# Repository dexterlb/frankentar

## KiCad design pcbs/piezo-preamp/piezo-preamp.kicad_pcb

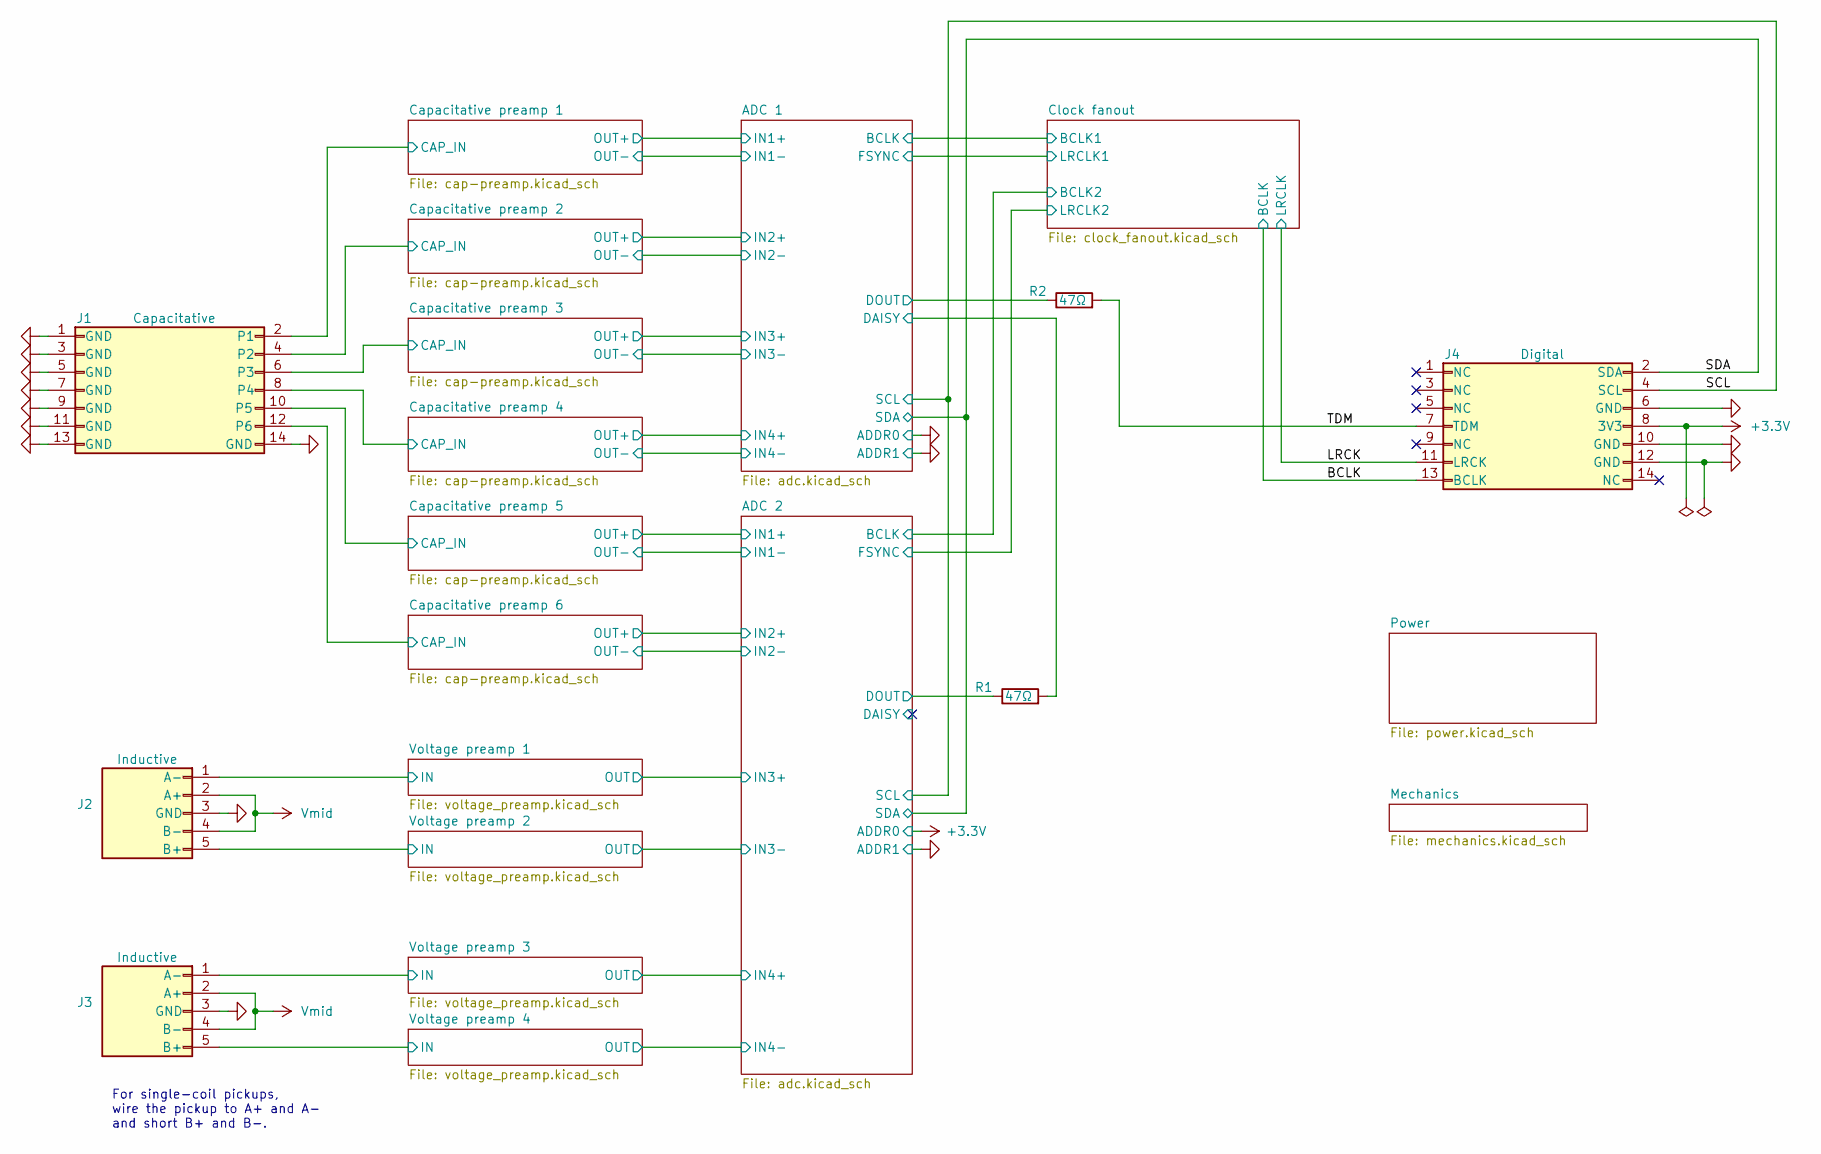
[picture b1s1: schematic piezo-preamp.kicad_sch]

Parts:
J1, J4: Conn_02x07_Odd_Even; PinHeader_2x07_P2.54mm_Vertical; MPN Header_02x07
J2, J3: Header_01x05; PinHeader_1x05_P2.54mm_Vertical
R1, R2: 47Ω; R_0805_2012Metric; MPN R 47Ω 125mW 1% 0805

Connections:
+3.3V: J4.8; also elsewhere on the board
/ADC 1/DAISY: R1.2; also elsewhere on the board
/ADC 1/DOUT: R2.1; also elsewhere on the board
/ADC 2/DOUT: R1.1; also elsewhere on the board
/BCLK: J4.13 (Pin_9); also elsewhere on the board
/Capacitative preamp 1/CAP_IN: J1.2; also elsewhere on the board
/Capacitative preamp 2/CAP_IN: J1.4; also elsewhere on the board
/Capacitative preamp 3/CAP_IN: J1.6; also elsewhere on the board
/Capacitative preamp 4/CAP_IN: J1.8; also elsewhere on the board
/Capacitative preamp 5/CAP_IN: J1.10; also elsewhere on the board
/Capacitative preamp 6/CAP_IN: J1.12; also elsewhere on the board
/LRCK: J4.11 (Pin_9); also elsewhere on the board
/SCL: J4.4; also elsewhere on the board
/SDA: J4.2; also elsewhere on the board
/TDM: J4.7, R2.2
/Voltage preamp 1/IN: J2.1; also elsewhere on the board
/Voltage preamp 2/IN: J2.5; also elsewhere on the board
/Voltage preamp 3/IN: J3.1; also elsewhere on the board
/Voltage preamp 4/IN: J3.5; also elsewhere on the board
GND: J1.1, J1.3, J1.5, J1.7, J1.9, J1.11 (Pin_9), J1.13 (Pin_9), J1.14 (Pin_12), J2.3, J3.3, J4.6, J4.10, J4.12; also elsewhere on the board
Vmid: J2.2, J2.4, J3.2, J3.4; also elsewhere on the board

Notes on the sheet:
For single-coil pickups, wire the pickup to A+ and A- and short B+ and B-.

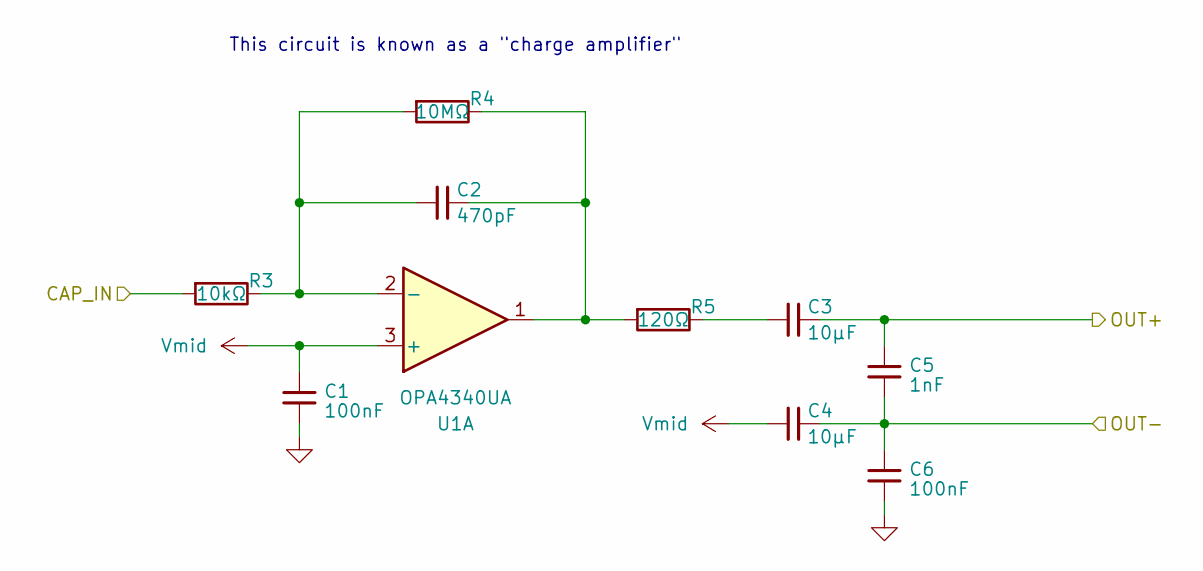
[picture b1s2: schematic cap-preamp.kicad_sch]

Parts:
C1, C6: 100nF; C_0805_2012Metric; MPN C 100nF 16V 0805
C2: 470pF; C_0805_2012Metric; MPN C 470pF 16V 0805; LCSC C1743
C3, C4: 10μF; C_0805_2012Metric; MPN C 10μF 50V 0805; LCSC C440198
C5: 1nF; C_0805_2012Metric; MPN C 1nF 16V 0805
R3: 10kΩ; R_0805_2012Metric; MPN R 10kΩ 125mW 1% 0805
R4: 10MΩ; R_0805_2012Metric; MPN R 10MΩ 125mW 1% 0805; LCSC C26108
R5: 120Ω; R_0805_2012Metric; MPN R 120Ω 125mW 1% 0805
U1: OPA4340UA; SOIC-14_3.9x8.7mm_P1.27mm; MPN OPA4340UA; LCSC C21713888

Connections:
/ADC 1/IN1+: C3.2, C5.1; also elsewhere on the board
/ADC 1/IN1-: C4.2, C5.2, C6.1; also elsewhere on the board
/Capacitative preamp 1/CAP_IN: R3.2; also elsewhere on the board
GND: C1.2, C6.2; also elsewhere on the board
unnamed: C2.2, R4.1, R5.2, U1.1
unnamed: C3.1, R5.1
unnamed 47: U1.7; also elsewhere on the board
unnamed 49: U1.8; also elsewhere on the board
unnamed 51: U1.14; also elsewhere on the board
unnamed: C2.1, R3.1, R4.2, U1.2 (-)
unnamed 64: U1.6 (-); also elsewhere on the board
unnamed 65: U1.9 (-); also elsewhere on the board
unnamed 66: U1.13 (-); also elsewhere on the board
Vmid: C1.1, C4.1, U1.3 (+), U1.5 (+), U1.10 (+), U1.12 (+); also elsewhere on the board

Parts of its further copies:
C16, C21, C22, C27, C28, C33, C43, C48, C49, C54: 100nF; C_0805_2012Metric; MPN C 100nF 16V 0805
C17, C23, C29, C44, C50: 470pF; C_0805_2012Metric; MPN C 470pF 16V 0805; LCSC C1743
C18, C19, C24, C25, C30, C31, C45, C46, C51, C52: 10μF; C_0805_2012Metric; MPN C 10μF 50V 0805; LCSC C440198
C20, C26, C32, C47, C53: 1nF; C_0805_2012Metric; MPN C 1nF 16V 0805
R6, R9, R12, R15, R18: 10kΩ; R_0805_2012Metric; MPN R 10kΩ 125mW 1% 0805
R7, R10, R13, R16, R19: 10MΩ; R_0805_2012Metric; MPN R 10MΩ 125mW 1% 0805; LCSC C26108
R8, R11, R14, R17, R20: 120Ω; R_0805_2012Metric; MPN R 120Ω 125mW 1% 0805

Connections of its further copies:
/ADC 1/IN2+: C18.2, C20.1; also elsewhere on the board
/ADC 1/IN2-: C19.2, C20.2, C21.1; also elsewhere on the board
/ADC 1/IN3+: C24.2, C26.1; also elsewhere on the board
/ADC 1/IN3-: C25.2, C26.2, C27.1; also elsewhere on the board
/ADC 1/IN4+: C30.2, C32.1; also elsewhere on the board
/ADC 1/IN4-: C31.2, C32.2, C33.1; also elsewhere on the board
/ADC 2/IN1+: C45.2, C47.1; also elsewhere on the board
/ADC 2/IN1-: C46.2, C47.2, C48.1; also elsewhere on the board
/ADC 2/IN2+: C51.2, C53.1; also elsewhere on the board
/ADC 2/IN2-: C52.2, C53.2, C54.1; also elsewhere on the board
/Capacitative preamp 2/CAP_IN: R6.2; also elsewhere on the board
/Capacitative preamp 3/CAP_IN: R9.2; also elsewhere on the board
/Capacitative preamp 4/CAP_IN: R12.2; also elsewhere on the board
/Capacitative preamp 5/CAP_IN: R15.2; also elsewhere on the board
/Capacitative preamp 6/CAP_IN: R18.2; also elsewhere on the board
GND: C16.2, C21.2, C22.2, C27.2, C28.2, C33.2, C43.2, C48.2, C49.2, C54.2; also elsewhere on the board
unnamed 47: C17.2, R7.1, R8.2; also elsewhere on the board
unnamed: C18.1, R8.1
unnamed 49: C23.2, R10.1, R11.2; also elsewhere on the board
unnamed: C24.1, R11.1
unnamed 51: C29.2, R13.1, R14.2; also elsewhere on the board
unnamed: C30.1, R14.1
unnamed 53: C44.2, R16.1, R17.2; also elsewhere on the board
unnamed: C45.1, R17.1
unnamed 55: C50.2, R19.1, R20.2; also elsewhere on the board
unnamed: C51.1, R20.1
unnamed 64: C17.1, R6.1, R7.2; also elsewhere on the board
unnamed 65: C23.1, R9.1, R10.2; also elsewhere on the board
unnamed 66: C29.1, R12.1, R13.2; also elsewhere on the board
unnamed 73: C44.1, R15.1, R16.2; also elsewhere on the board
unnamed 74: C50.1, R18.1, R19.2; also elsewhere on the board
Vmid: C16.1, C19.1, C22.1, C25.1, C28.1, C31.1, C43.1, C46.1, C49.1, C52.1; also elsewhere on the board

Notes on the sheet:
This circuit is known as a "charge amplifier"

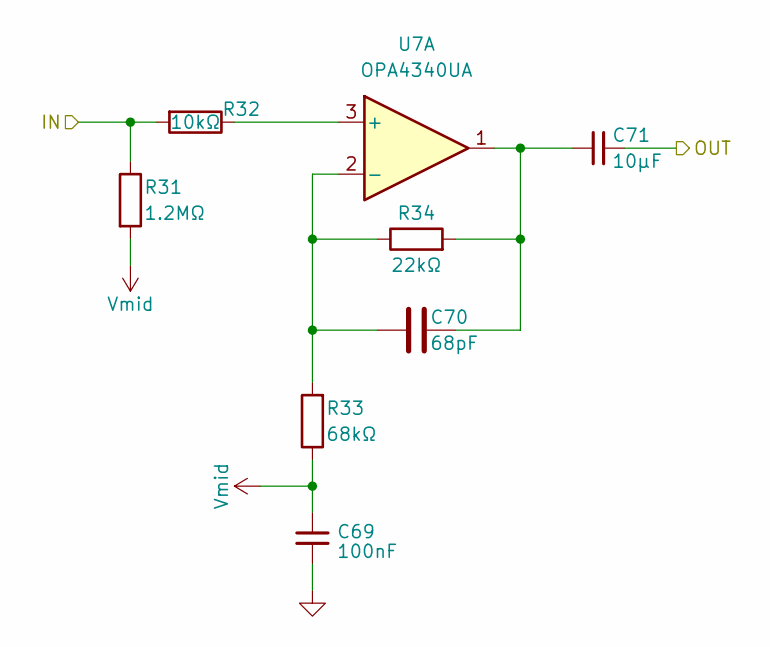
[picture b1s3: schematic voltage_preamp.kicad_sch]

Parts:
C69: 100nF; C_0805_2012Metric; MPN C 100nF 16V 0805
C70: 68pF; C_0805_2012Metric; MPN C 68pF 50V 0805
C71: 10μF; C_0805_2012Metric; MPN C 10μF 50V 0805; LCSC C440198
R31: 1.2MΩ; R_0805_2012Metric; MPN R 1.2MΩ 125mW 1% 0805
R32: 10kΩ; R_0805_2012Metric; MPN R 10kΩ 125mW 1% 0805
R33: 68kΩ; R_0805_2012Metric; MPN R 68kΩ 125mW 1% 0805
R34: 22kΩ; R_0805_2012Metric; MPN R 22kΩ 125mW 1% 0805
U7: OPA4340UA; SOIC-14_3.9x8.7mm_P1.27mm; MPN OPA4340UA; LCSC C21713888

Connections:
/ADC 2/IN3+: C71.2; also elsewhere on the board
/Voltage preamp 1/IN: R31.1, R32.2; also elsewhere on the board
GND: C69.2; also elsewhere on the board
unnamed: C70.1, C71.1, R34.2, U7.1
unnamed 58: U7.7; also elsewhere on the board
unnamed 59: U7.8; also elsewhere on the board
unnamed 60: U7.14; also elsewhere on the board
unnamed: R32.1, U7.3 (+)
unnamed: C70.2, R33.2, R34.1, U7.2 (-)
unnamed 86: U7.5 (+); also elsewhere on the board
unnamed 87: U7.6 (-); also elsewhere on the board
unnamed 88: U7.10 (+); also elsewhere on the board
unnamed 89: U7.9 (-); also elsewhere on the board
unnamed 90: U7.12 (+); also elsewhere on the board
unnamed 91: U7.13 (-); also elsewhere on the board
Vmid: C69.1, R31.2, R33.1; also elsewhere on the board

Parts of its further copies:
C72, C75, C78: 100nF; C_0805_2012Metric; MPN C 100nF 16V 0805
C73, C76, C79: 68pF; C_0805_2012Metric; MPN C 68pF 50V 0805
C74, C77, C80: 10μF; C_0805_2012Metric; MPN C 10μF 50V 0805; LCSC C440198
R35, R39, R43: 1.2MΩ; R_0805_2012Metric; MPN R 1.2MΩ 125mW 1% 0805
R36, R40, R44: 10kΩ; R_0805_2012Metric; MPN R 10kΩ 125mW 1% 0805
R37, R41, R45: 68kΩ; R_0805_2012Metric; MPN R 68kΩ 125mW 1% 0805
R38, R42, R46: 22kΩ; R_0805_2012Metric; MPN R 22kΩ 125mW 1% 0805

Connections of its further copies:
/ADC 2/IN3-: C74.2; also elsewhere on the board
/ADC 2/IN4+: C77.2; also elsewhere on the board
/ADC 2/IN4-: C80.2; also elsewhere on the board
/Voltage preamp 2/IN: R35.1, R36.2; also elsewhere on the board
/Voltage preamp 3/IN: R39.1, R40.2; also elsewhere on the board
/Voltage preamp 4/IN: R43.1, R44.2; also elsewhere on the board
GND: C72.2, C75.2, C78.2; also elsewhere on the board
unnamed 58: C73.1, C74.1, R38.2; also elsewhere on the board
unnamed 59: C76.1, C77.1, R42.2; also elsewhere on the board
unnamed 60: C79.1, C80.1, R46.2; also elsewhere on the board
unnamed 86: R36.1; also elsewhere on the board
unnamed 87: C73.2, R37.2, R38.1; also elsewhere on the board
unnamed 88: R40.1; also elsewhere on the board
unnamed 89: C76.2, R41.2, R42.1; also elsewhere on the board
unnamed 90: R44.1; also elsewhere on the board
unnamed 91: C79.2, R45.2, R46.1; also elsewhere on the board
Vmid: C72.1, C75.1, C78.1, R35.2, R37.1, R39.2, R41.1, R43.2, R45.1; also elsewhere on the board

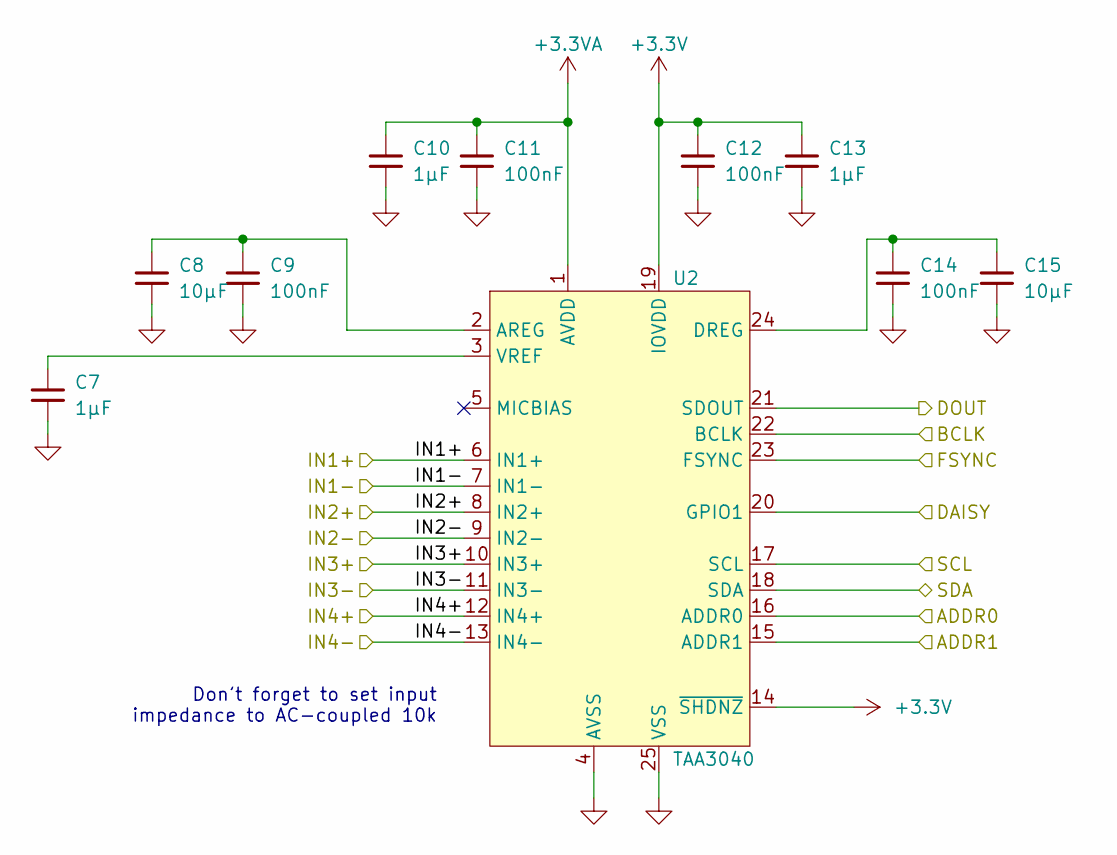
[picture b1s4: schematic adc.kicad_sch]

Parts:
C7, C10, C13: 1μF; C_0805_2012Metric; MPN C 1μF 16V 0805
C8, C15: 10μF; C_0805_2012Metric; MPN C 10μF 16V 0805
C9, C11, C12, C14: 100nF; C_0805_2012Metric; MPN C 100nF 16V 0805
U2: TAA3040; WQFN-24-1EP_4x4mm_P0.5mm_EP2.6x2.6mm; MPN TAA3040IRTWR; LCSC C43656726

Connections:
+3.3V: C12.1, C13.1, U2.14 (~SHDNZ), U2.19 (IOVDD); also elsewhere on the board
+3.3VA: C10.1, C11.1, U2.1 (AVDD); also elsewhere on the board
/ADC 1/BCLK: U2.22 (BCLK); also elsewhere on the board
/ADC 1/DAISY: U2.20 (GPIO1); also elsewhere on the board
/ADC 1/DOUT: U2.21 (SDOUT); also elsewhere on the board
/ADC 1/FSYNC: U2.23 (FSYNC); also elsewhere on the board
/ADC 1/IN1+: U2.6 (IN1+); also elsewhere on the board
/ADC 1/IN1-: U2.7 (IN1-); also elsewhere on the board
/ADC 1/IN2+: U2.8 (IN2+); also elsewhere on the board
/ADC 1/IN2-: U2.9 (IN2-); also elsewhere on the board
/ADC 1/IN3+: U2.10 (IN3+); also elsewhere on the board
/ADC 1/IN3-: U2.11 (IN3-); also elsewhere on the board
/ADC 1/IN4+: U2.12 (IN4+); also elsewhere on the board
/ADC 1/IN4-: U2.13 (IN4-); also elsewhere on the board
/SCL: U2.17 (SCL); also elsewhere on the board
/SDA: U2.18 (SDA); also elsewhere on the board
GND: C7.2, C8.2, C9.2, C10.2, C11.2, C12.2, C13.2, C14.2, C15.2, U2.4 (AVSS), U2.15 (ADDR1), U2.16 (ADDR0), U2.25 (VSS); also elsewhere on the board
unnamed: C8.1, C9.1, U2.2 (AREG)
unnamed: C14.1, C15.1, U2.24 (DREG)
unnamed: C7.1, U2.3 (VREF)

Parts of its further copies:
C34, C37, C40: 1μF; C_0805_2012Metric; MPN C 1μF 16V 0805
C35, C42: 10μF; C_0805_2012Metric; MPN C 10μF 16V 0805
C36, C38, C39, C41: 100nF; C_0805_2012Metric; MPN C 100nF 16V 0805
U3: TAA3040; WQFN-24-1EP_4x4mm_P0.5mm_EP2.6x2.6mm; MPN TAA3040IRTWR; LCSC C43656726

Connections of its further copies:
+3.3V: C39.1, C40.1, U3.14 (~SHDNZ), U3.16 (ADDR0), U3.19 (IOVDD); also elsewhere on the board
+3.3VA: C37.1, C38.1, U3.1 (AVDD); also elsewhere on the board
/ADC 2/BCLK: U3.22 (BCLK); also elsewhere on the board
/ADC 2/DAISY: U3.20 (GPIO1)
/ADC 2/DOUT: U3.21 (SDOUT); also elsewhere on the board
/ADC 2/FSYNC: U3.23 (FSYNC); also elsewhere on the board
/ADC 2/IN1+: U3.6 (IN1+); also elsewhere on the board
/ADC 2/IN1-: U3.7 (IN1-); also elsewhere on the board
/ADC 2/IN2+: U3.8 (IN2+); also elsewhere on the board
/ADC 2/IN2-: U3.9 (IN2-); also elsewhere on the board
/ADC 2/IN3+: U3.10 (IN3+); also elsewhere on the board
/ADC 2/IN3-: U3.11 (IN3-); also elsewhere on the board
/ADC 2/IN4+: U3.12 (IN4+); also elsewhere on the board
/ADC 2/IN4-: U3.13 (IN4-); also elsewhere on the board
/SCL: U3.17 (SCL); also elsewhere on the board
/SDA: U3.18 (SDA); also elsewhere on the board
GND: C34.2, C35.2, C36.2, C37.2, C38.2, C39.2, C40.2, C41.2, C42.2, U3.4 (AVSS), U3.15 (ADDR1), U3.25 (VSS); also elsewhere on the board
unnamed: C35.1, C36.1, U3.2 (AREG)
unnamed: C41.1, C42.1, U3.24 (DREG)
unnamed: C34.1, U3.3 (VREF)

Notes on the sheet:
Don't forget to set input impedance to AC-coupled 10k

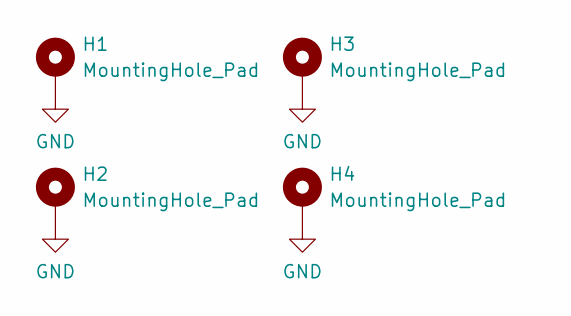
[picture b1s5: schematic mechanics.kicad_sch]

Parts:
H1, H2, H3, H4: MountingHole_Pad; MountingHole_3.2mm_M3_Pad_Via

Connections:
GND: H1.1 (1_1), H2.1 (1_1), H3.1 (1_1), H4.1 (1_1); also elsewhere on the board

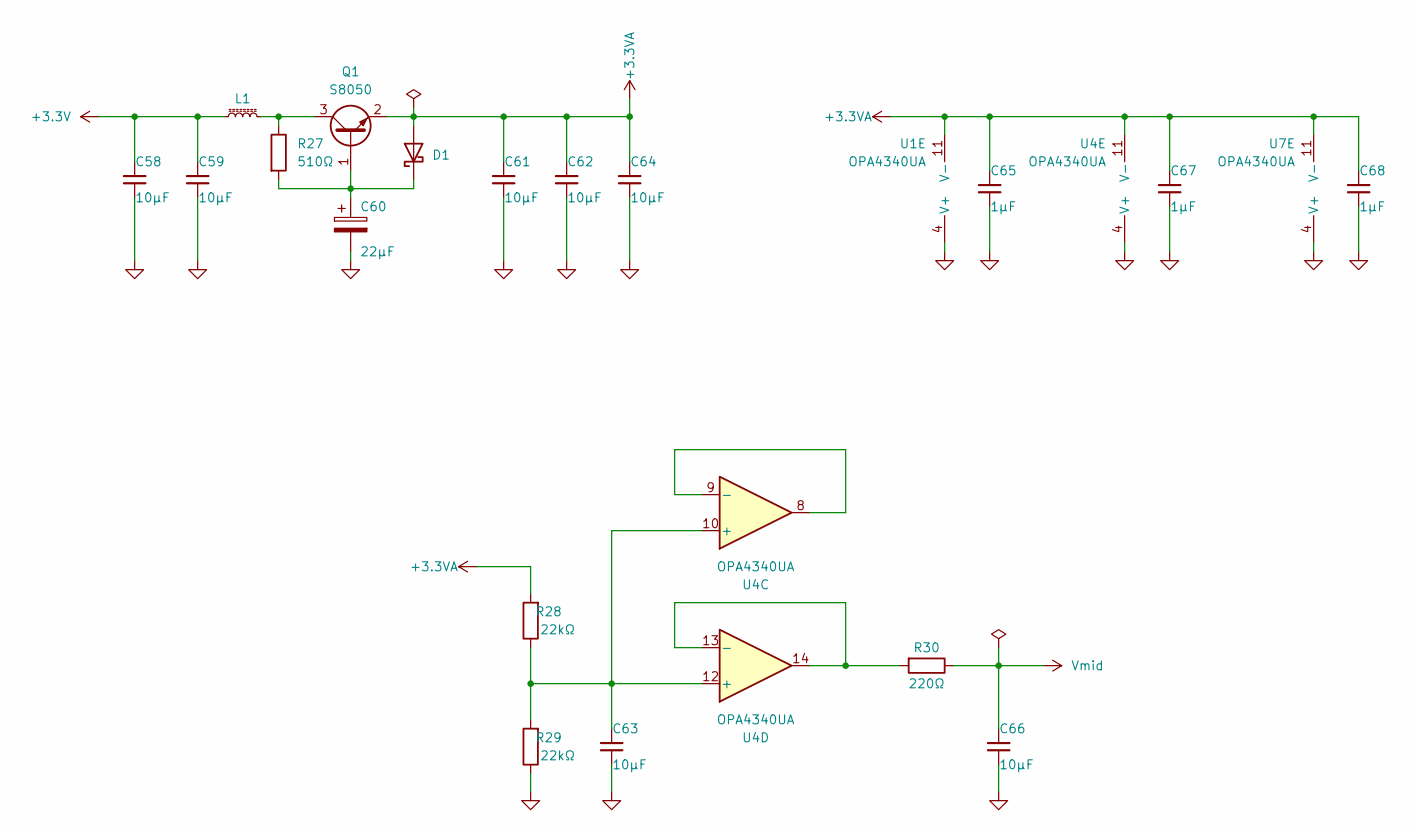
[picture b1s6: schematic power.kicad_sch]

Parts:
C58, C59, C61, C62, C63, C64, C66: 10μF; C_0805_2012Metric; MPN C 10μF 16V 0805
C60: 22μF; C_0805_2012Metric; MPN C 22μF 16V 0805
C65, C67, C68: 1μF; C_0805_2012Metric; MPN C 1μF 16V 0805
D1: Schottky; D_SOD-123; MPN B0540W
L1: 600@100Mhz; L_0805_2012Metric; MPN BLM21AG601SN1D
Q1: S8050; SOT-23; MPN BC817-40
R27: 510Ω; R_0805_2012Metric; MPN R 510Ω 125mW 1% 0805
R28, R29: 22kΩ; R_0805_2012Metric; MPN R 22kΩ 125mW 1% 0805
R30: 220Ω; R_0805_2012Metric; MPN R 220Ω 125mW 1% 0805
U1, U4, U7: OPA4340UA; SOIC-14_3.9x8.7mm_P1.27mm; MPN OPA4340UA; LCSC C21713888

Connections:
+3.3V: C58.1, C59.1, L1.1; also elsewhere on the board
+3.3VA: C61.1, C62.1, C64.1, C65.1, C67.1, C68.1, D1.2 (A), Q1.2 (E), R28.2, U1.11 (V-), U4.11 (V-), U7.11 (V-); also elsewhere on the board
GND: C58.2, C59.2, C60.2, C61.2, C62.2, C63.2, C64.2, C65.2, C66.2, C67.2, C68.2, R29.1, U1.4 (V+), U4.4 (V+), U7.4 (V+); also elsewhere on the board
unnamed 47: U1.7; also elsewhere on the board
unnamed 49: U1.8; also elsewhere on the board
unnamed 51: U1.14; also elsewhere on the board
unnamed 55: U4.7; also elsewhere on the board
unnamed 58: U7.7; also elsewhere on the board
unnamed 59: U7.8; also elsewhere on the board
unnamed 60: U7.14; also elsewhere on the board
unnamed: C60.1, D1.1 (K), Q1.1 (B), R27.2
unnamed: L1.2, Q1.3 (C), R27.1
unnamed 64: U1.6 (-); also elsewhere on the board
unnamed 65: U1.9 (-); also elsewhere on the board
unnamed 66: U1.13 (-); also elsewhere on the board
unnamed 74: U4.6 (-); also elsewhere on the board
unnamed: C63.1, R28.1, R29.2, U4.10 (+), U4.12 (+)
unnamed: U4.8, U4.9 (-)
unnamed: R30.2, U4.13 (-), U4.14
unnamed 86: U7.5 (+); also elsewhere on the board
unnamed 87: U7.6 (-); also elsewhere on the board
unnamed 88: U7.10 (+); also elsewhere on the board
unnamed 89: U7.9 (-); also elsewhere on the board
unnamed 90: U7.12 (+); also elsewhere on the board
unnamed 91: U7.13 (-); also elsewhere on the board
Vmid: C66.1, R30.1, U1.5 (+), U1.10 (+), U1.12 (+), U4.5 (+); also elsewhere on the board

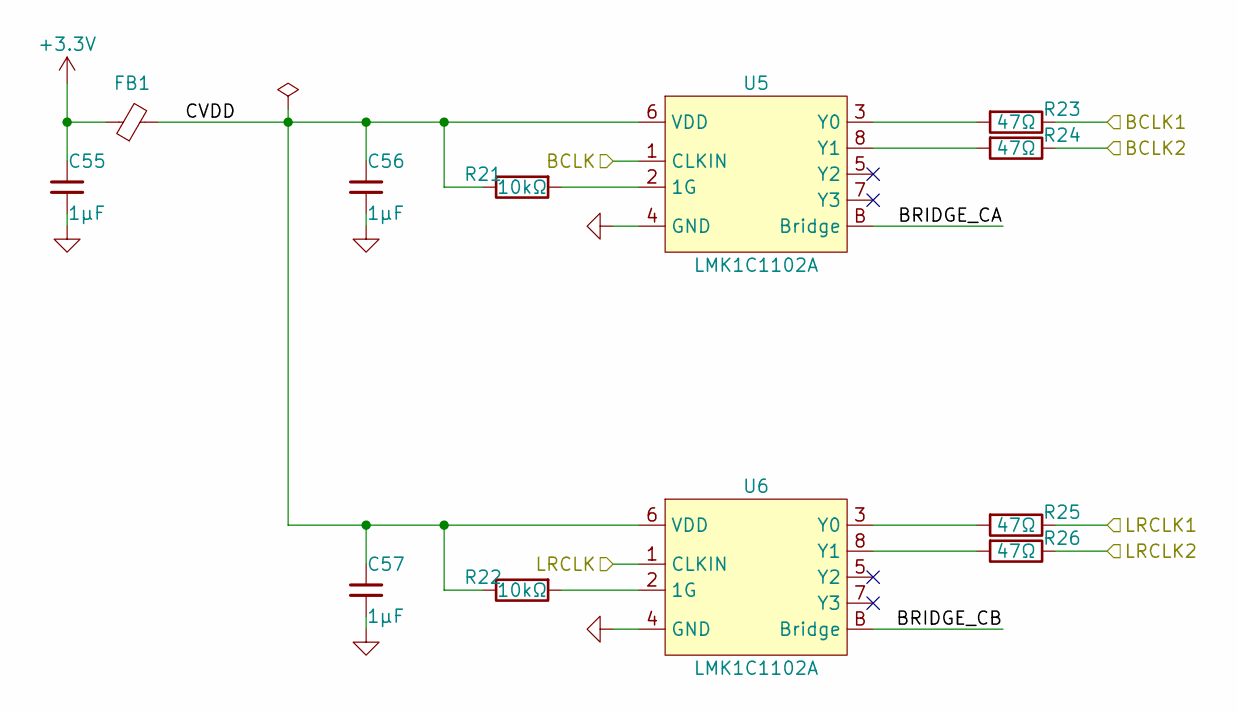
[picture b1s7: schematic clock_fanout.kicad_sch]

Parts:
C55, C56, C57: 1μF; C_0805_2012Metric; MPN C 1μF 16V 0805
FB1: FerriteBead_Small; L_0805_2012Metric; MPN BLM21AG102SN1D
R21, R22: 10kΩ; R_0805_2012Metric; MPN R 10kΩ 125mW 1% 0805
R23, R24, R25, R26: 47Ω; R_0805_2012Metric; MPN R 47Ω 125mW 1% 0805
U5, U6: LMK1C1102A; TSSOP-8_4.4x3mm_P0.65mm_bridges; MPN LMK1C1102APWR

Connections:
+3.3V: C55.1, FB1.1; also elsewhere on the board
/ADC 1/BCLK: R23.1; also elsewhere on the board
/ADC 1/FSYNC: R25.1; also elsewhere on the board
/ADC 2/BCLK: R24.1; also elsewhere on the board
/ADC 2/FSYNC: R26.1; also elsewhere on the board
/BCLK: U5.1 (CLKIN); also elsewhere on the board
/Clock fanout/BRIDGE_CA: U5.B (Bridge)
/Clock fanout/BRIDGE_CB: U6.B (Bridge)
/Clock fanout/CVDD: C56.1, C57.1, FB1.2, R21.1, R22.1, U5.6 (VDD), U6.6 (VDD)
/LRCK: U6.1 (CLKIN); also elsewhere on the board
GND: C55.2, C56.2, C57.2, U5.4 (GND), U6.4 (GND); also elsewhere on the board
unnamed: R21.2, U5.2 (1G)
unnamed: R23.2, U5.3 (Y0)
unnamed: R24.2, U5.8 (Y1)
unnamed: R22.2, U6.2 (1G)
unnamed: R25.2, U6.3 (Y0)
unnamed: R26.2, U6.8 (Y1)

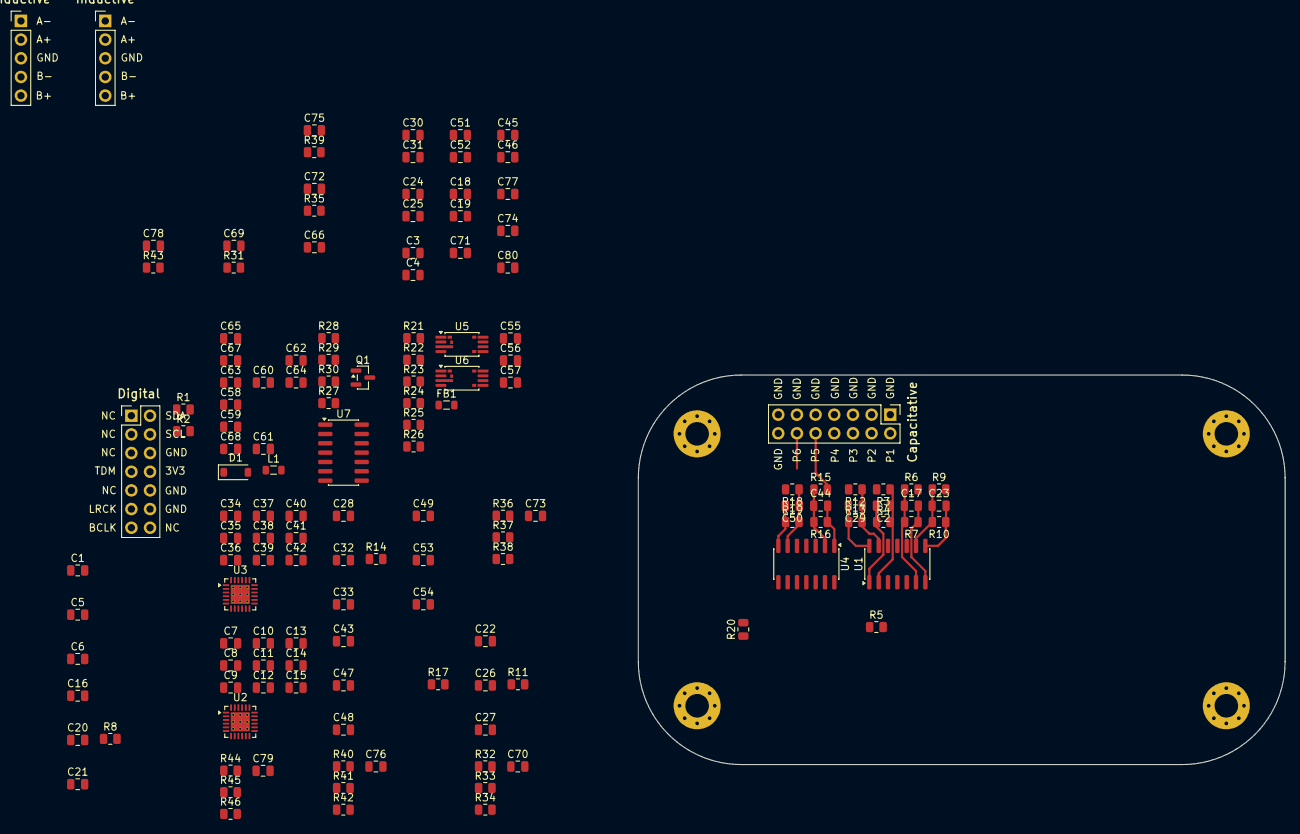
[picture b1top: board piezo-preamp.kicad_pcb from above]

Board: 4 copper layers, 88.0 x 53.0 mm, 145 parts (0 on the bottom side), 90 nets.

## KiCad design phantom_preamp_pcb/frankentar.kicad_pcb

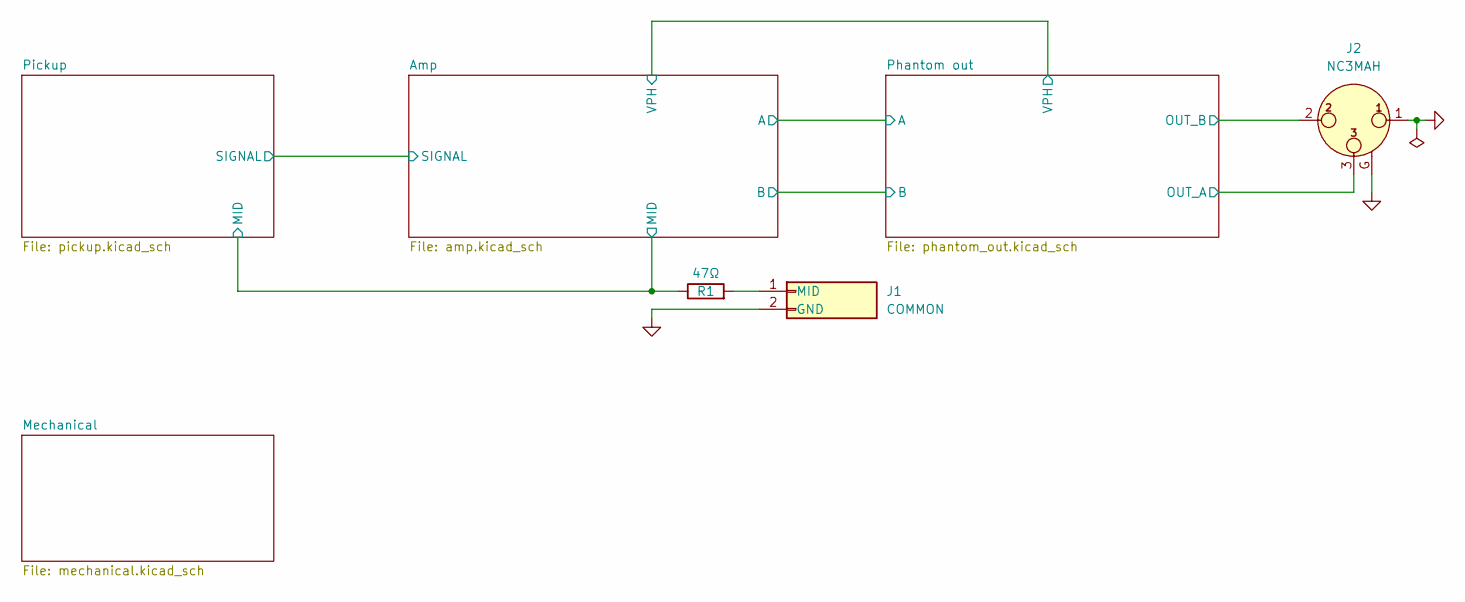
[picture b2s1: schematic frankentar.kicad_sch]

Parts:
J1: Header_01x02; mta100_01x2_P2.54_647050-2; Part 640456-2
J2: NC3MAH; Jack_XLR_Neutrik_NC3MAH_Horizontal; Part NC3MAH
R1: 47Ω; R_0805_2012Metric; Part R 47Ω 125mW 1% 0805

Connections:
/Amp/MID: R1.1; also elsewhere on the board
/Phantom out/OUT_A: J2.3; also elsewhere on the board
/Phantom out/OUT_B: J2.2; also elsewhere on the board
GND: J1.2, J2.1, J2.G; also elsewhere on the board
unnamed: J1.1, R1.2

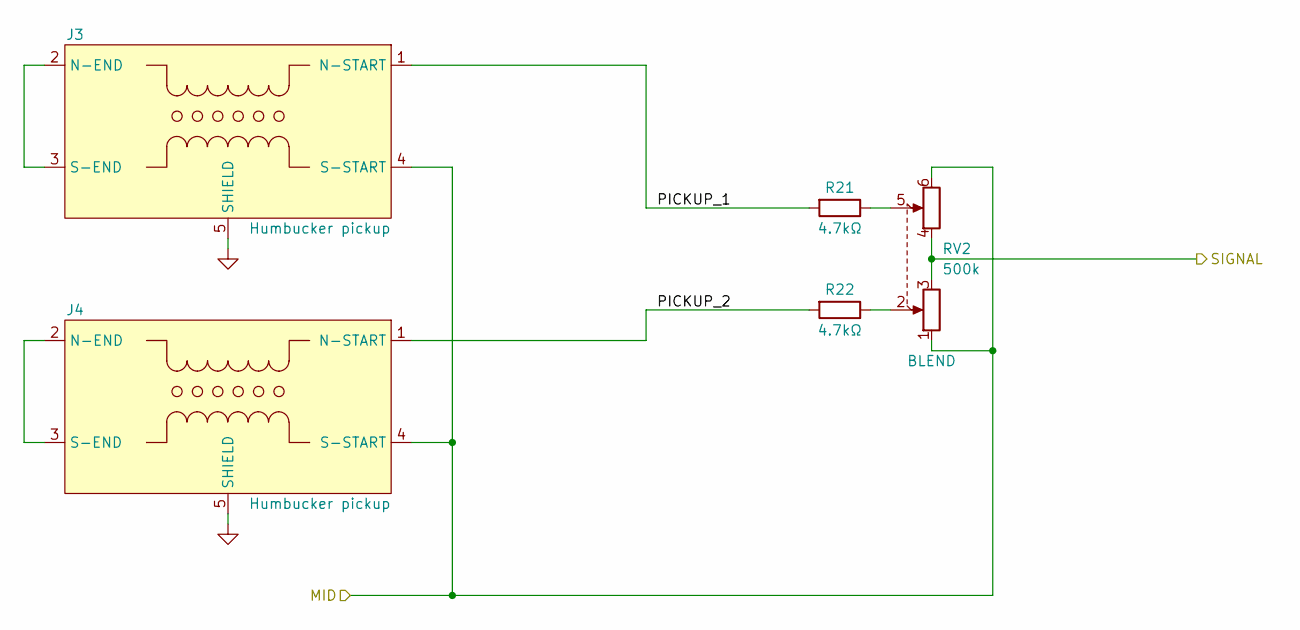
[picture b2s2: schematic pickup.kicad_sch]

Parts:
J3, J4: Humbucker pickup; mta100_01x5_P2.54_647050-5; Part 640456-5
R21, R22: 4.7kΩ; R_0805_2012Metric; Part R 4.7kΩ 125mW 1% 0805
RV2: 500k; Potentiometer_Bourns_PDB182-K_Dual_Horizontal; Part PDB182-K420K-504B

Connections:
/Amp/MID: J3.4 (S-START), J4.4 (S-START), RV2.1, RV2.6; also elsewhere on the board
/Amp/SIGNAL: RV2.3, RV2.4; also elsewhere on the board
/Pickup/PICKUP_1: J3.1 (N-START), R21.2
/Pickup/PICKUP_2: J4.1 (N-START), R22.2
GND: J3.5 (SHIELD), J4.5 (SHIELD); also elsewhere on the board
unnamed: J3.2 (N-END), J3.3 (S-END)
unnamed: J4.2 (N-END), J4.3 (S-END)
unnamed: R21.1, RV2.5
unnamed: R22.1, RV2.2

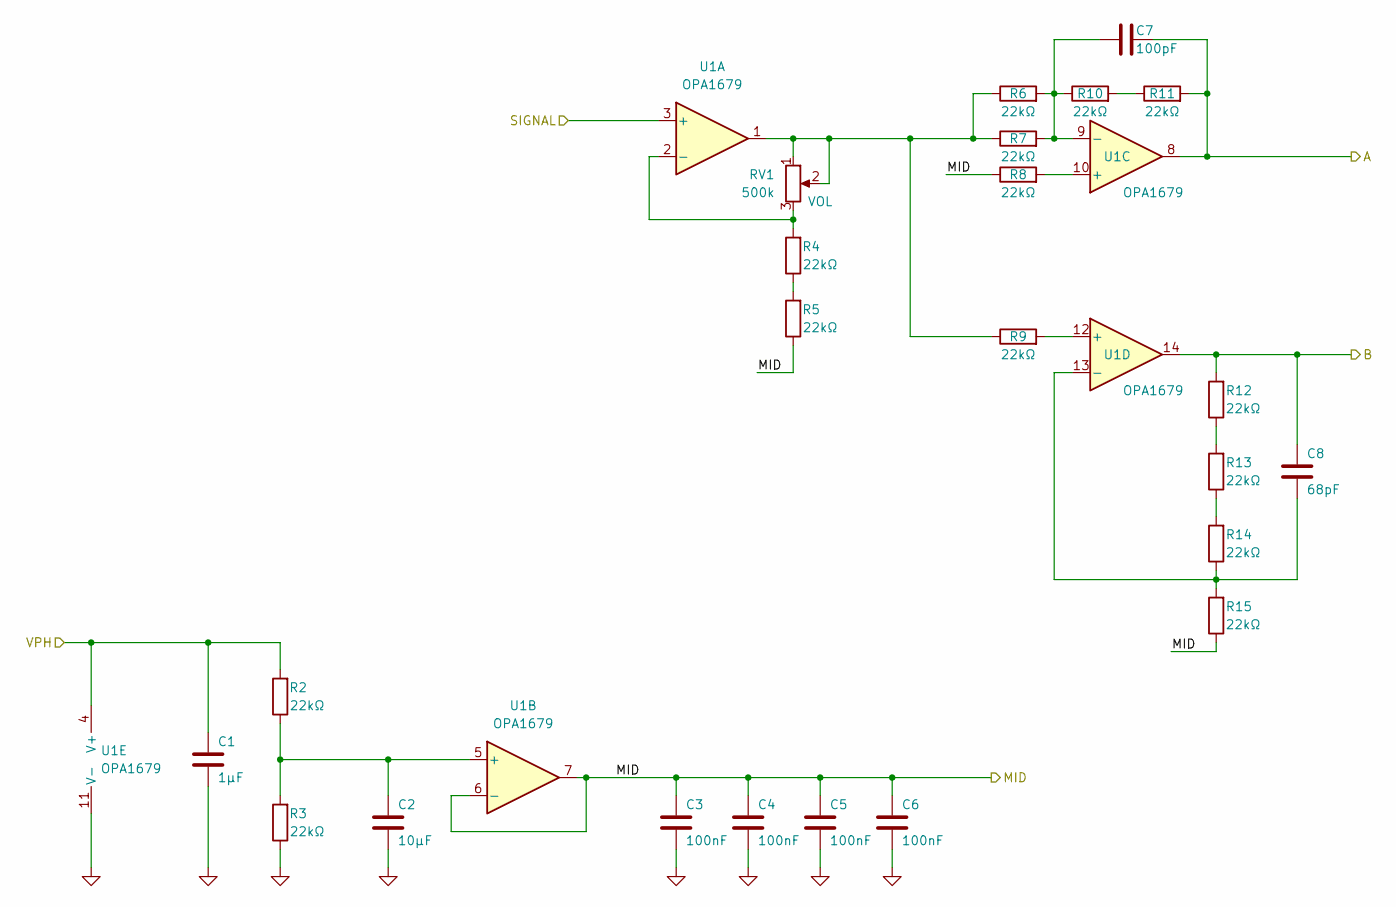
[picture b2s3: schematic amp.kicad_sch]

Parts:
C1: 1μF; C_0805_2012Metric; MPN C 1μF 50V 0805
C2: 10μF; C_0805_2012Metric; MPN C 10μF 50V 0805
C3, C4, C5, C6: 100nF; C_0805_2012Metric; MPN C 100nF 50V 0805
C7: 100pF; C_0805_2012Metric; MPN C 100pF 50V 0805
C8: 68pF; C_0805_2012Metric; MPN C 68pF 50V 0805
R2, R3, R4, R5, R6, R7, R8, R9, R10, R11, R12, R13, R14, R15: 22kΩ; R_0805_2012Metric; MPN R 22kΩ 125mW 1% 0805
RV1: 500k; Potentiometer_Bourns_PDB181-K_Single_Horizontal; MPN PDB181-K420K-504A2
U1: OPA1679; SOIC-14_3.9x8.7mm_P1.27mm; MPN OPA1679IDR

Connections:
/Amp/A: C7.2, R11.2, U1.8; also elsewhere on the board
/Amp/B: C8.2, R12.2, U1.14; also elsewhere on the board
/Amp/MID: C3.1, C4.1, C5.1, C6.1, R5.1, R8.1, R15.1, U1.6 (-), U1.7; also elsewhere on the board
/Amp/SIGNAL: U1.3 (+); also elsewhere on the board
/Amp/VPH: C1.1, R2.2, U1.4 (V+); also elsewhere on the board
GND: C1.2, C2.2, C3.2, C4.2, C5.2, C6.2, R3.1, U1.11 (V-); also elsewhere on the board
unnamed: R4.1, R5.2
unnamed: R6.1, R7.1, R9.1, RV1.1, RV1.2, U1.1
unnamed: R10.2, R11.1
unnamed: R12.1, R13.2
unnamed: R13.1, R14.2
unnamed: R4.2, RV1.3, U1.2 (-)
unnamed: C2.1, R2.1, R3.2, U1.5 (+)
unnamed: R8.2, U1.10 (+)
unnamed: C7.1, R6.2, R7.2, R10.1, U1.9 (-)
unnamed: R9.2, U1.12 (+)
unnamed: C8.1, R14.1, R15.2, U1.13 (-)

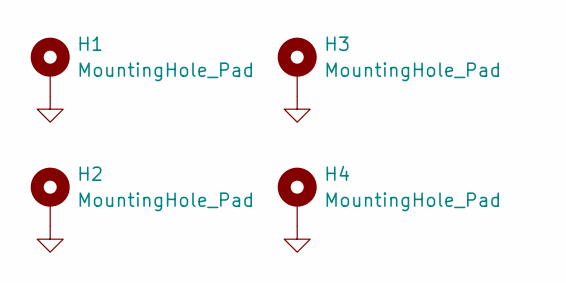
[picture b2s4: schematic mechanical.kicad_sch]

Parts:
H1, H2, H3, H4: MountingHole_Pad; MountingHole_3.2mm_M3_Pad_Via

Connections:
GND: H1.1, H2.1, H3.1, H4.1; also elsewhere on the board

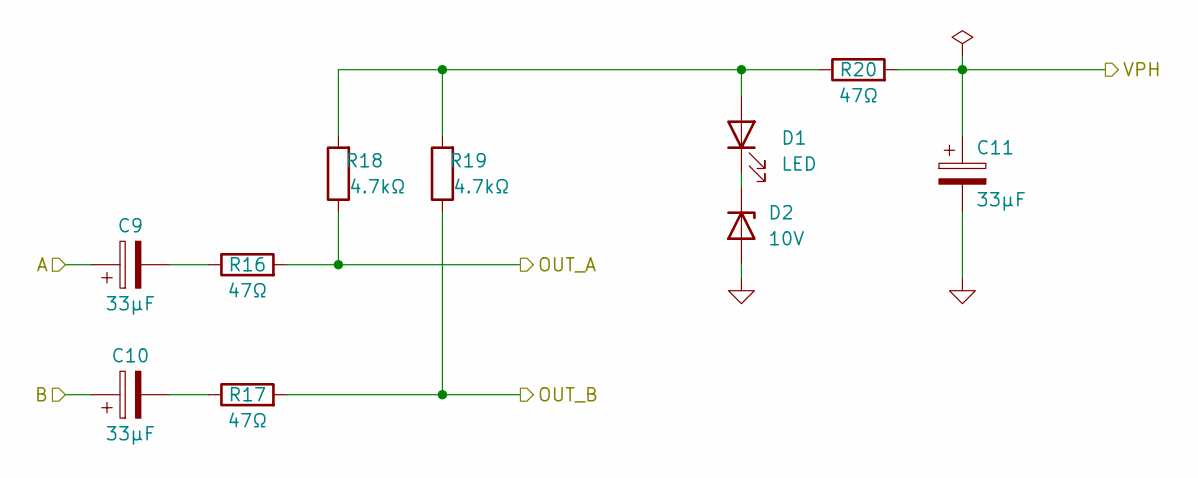
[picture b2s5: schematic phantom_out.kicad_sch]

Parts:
C9, C10, C11: 33μF; CP_Radial_D8.0mm_P3.50mm; Part CP 33μF 100V P3.5 AUDIO
D1: LED; LED_0805_2012Metric; Part KP-2012SECK
D2: 10V; D_MiniMELF; Part TZMC10GS08
R16, R17, R20: 47Ω; R_0805_2012Metric; Part R 47Ω 125mW 1% 0805
R18, R19: 4.7kΩ; R_0805_2012Metric; Part R 4.7kΩ 125mW 1% 0805

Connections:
/Amp/A: C9.1; also elsewhere on the board
/Amp/B: C10.1; also elsewhere on the board
/Amp/VPH: C11.1, R20.2; also elsewhere on the board
/Phantom out/OUT_A: R16.2, R18.1; also elsewhere on the board
/Phantom out/OUT_B: R17.2, R19.1; also elsewhere on the board
GND: C11.2, D2.2 (A); also elsewhere on the board
unnamed: C9.2, R16.1
unnamed: C10.2, R17.1
unnamed: D1.2 (A), R18.2, R19.2, R20.1
unnamed: D1.1 (K), D2.1 (K)
